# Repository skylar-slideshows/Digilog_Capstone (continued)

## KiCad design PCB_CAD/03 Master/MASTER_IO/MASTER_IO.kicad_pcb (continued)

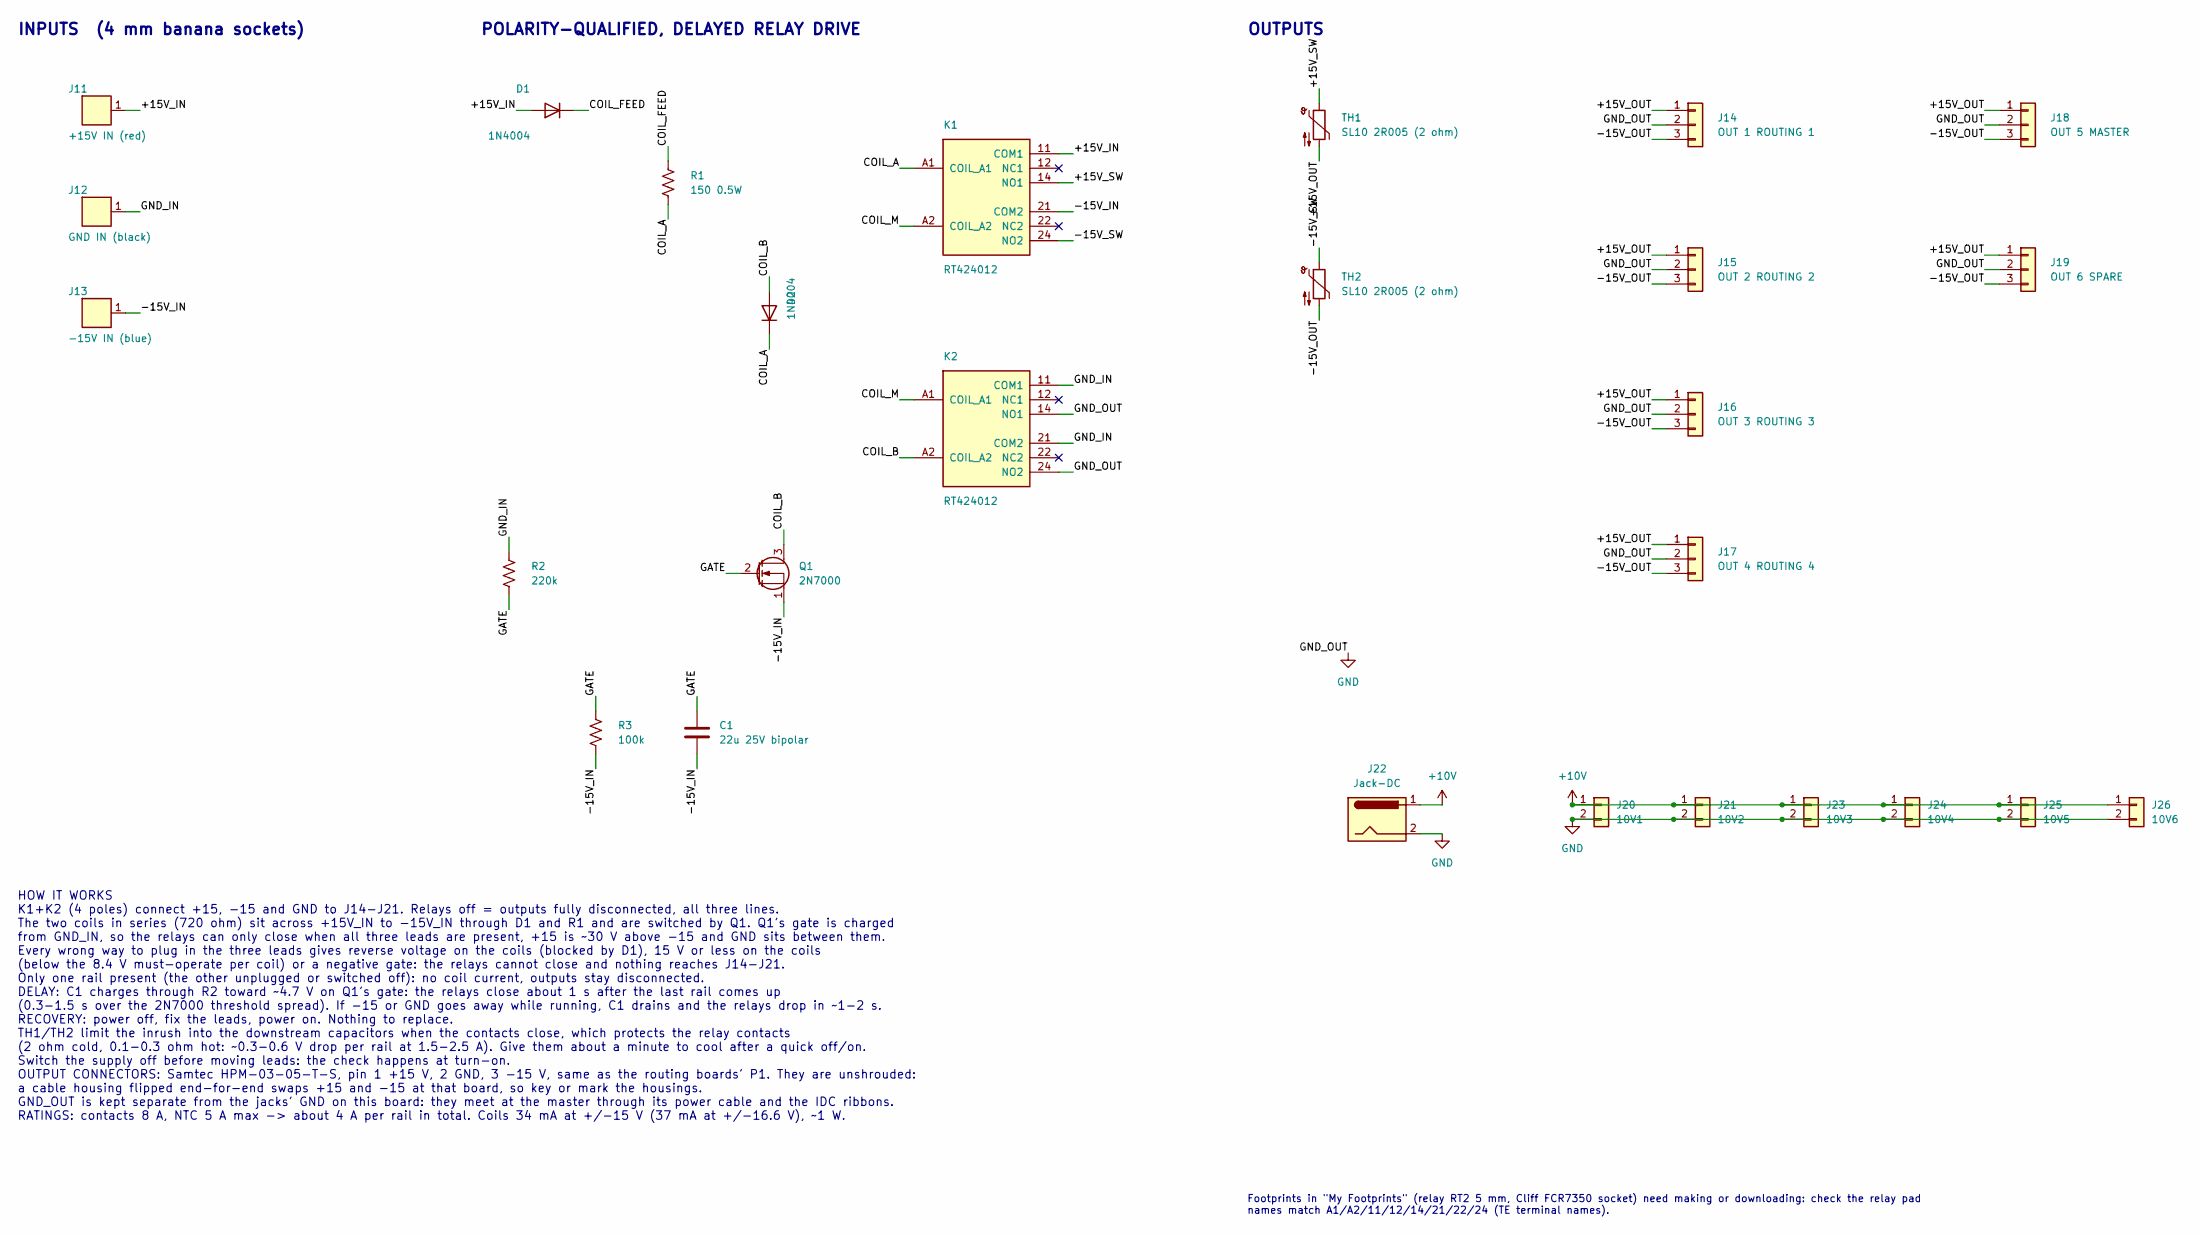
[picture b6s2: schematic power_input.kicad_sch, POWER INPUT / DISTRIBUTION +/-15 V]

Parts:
C1: 22u 25V bipolar; C_Radial_D6.3mm_H11.0mm_P2.50mm; MPN ECA-1EEN220
D1, D2: 1N4004; D_DO-41_SOD81_P10.16mm_Horizontal; MPN 1N4004G
J11: +15V IN (red); FCR7350; MPN FCR7350R
J12: GND IN (black); FCR7350; MPN FCR7350B
J13: -15V IN (blue); FCR7350; MPN FCR7350L
J14: OUT 1 ROUTING 1; Samtec_HPM-03-05-x-S_Straight_1x03_Pitch5.08mm; MPN HPM-03-05-T-S
J15: OUT 2 ROUTING 2; Samtec_HPM-03-05-x-S_Straight_1x03_Pitch5.08mm; MPN HPM-03-05-T-S
J16: OUT 3 ROUTING 3; Samtec_HPM-03-05-x-S_Straight_1x03_Pitch5.08mm; MPN HPM-03-05-T-S
J17: OUT 4 ROUTING 4; Samtec_HPM-03-05-x-S_Straight_1x03_Pitch5.08mm; MPN HPM-03-05-T-S
J18: OUT 5 MASTER; Samtec_HPM-03-05-x-S_Straight_1x03_Pitch5.08mm; MPN HPM-03-05-T-S
J19: OUT 6 SPARE; Samtec_HPM-03-05-x-S_Straight_1x03_Pitch5.08mm; MPN HPM-03-05-T-S
J20: 10V1; PinHeader_1x02_P2.54mm_Vertical
J21: 10V2; PinHeader_1x02_P2.54mm_Vertical
J22: Jack-DC; BarrelJack_Horizontal
J23: 10V3; PinHeader_1x02_P2.54mm_Vertical
J24: 10V4; PinHeader_1x02_P2.54mm_Vertical
J25: 10V5; PinHeader_1x02_P2.54mm_Vertical
J26: 10V6; PinHeader_1x02_P2.54mm_Vertical
K1, K2: RT424012; Relay_DPDT_Schrack-RT2-FormC_RM5mm; MPN RT424012
Q1: 2N7000; TO-92_Inline_Wide; MPN 2N7000
R1: 150 0.5W; R_Axial_DIN0309_L9.0mm_D3.2mm_P12.70mm_Horizontal; MPN MFR50SFTE52-150R
R2: 220k; R_Axial_DIN0207_L6.3mm_D2.5mm_P10.16mm_Horizontal; MPN MFR-25FBF52-220K
R3: 100k; R_Axial_DIN0207_L6.3mm_D2.5mm_P10.16mm_Horizontal; MPN MFR-25FBF52-100K
TH1, TH2: SL10 2R005 (2 ohm); C_Disc_D10.0mm_W2.5mm_P5.00mm; MPN SL10 2R005

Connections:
+10V: J20.1, J21.1, J22.1, J23.1, J24.1, J25.1, J26.1
/POWER INPUT +/-15V/+15V_IN: D1.2 (A), J11.1 (~_1), K1.11 (COM1)
/POWER INPUT +/-15V/+15V_OUT: J14.1, J15.1, J16.1, J17.1, J18.1, J19.1, TH1.2
/POWER INPUT +/-15V/+15V_SW: K1.14 (NO1), TH1.1
/POWER INPUT +/-15V/-15V_IN: C1.2, J13.1 (~_1), K1.21 (COM2), Q1.1 (S), R3.2
/POWER INPUT +/-15V/-15V_OUT: J14.3, J15.3, J16.3, J17.3, J18.3, J19.3, TH2.2
/POWER INPUT +/-15V/-15V_SW: K1.24 (NO2), TH2.1
/POWER INPUT +/-15V/COIL_A: D2.1 (K), K1.A1 (COIL_A1), R1.2
/POWER INPUT +/-15V/COIL_B: D2.2 (A), K2.A2 (COIL_A2), Q1.3 (D)
/POWER INPUT +/-15V/COIL_FEED: D1.1 (K), R1.1
/POWER INPUT +/-15V/COIL_M: K1.A2 (COIL_A2), K2.A1 (COIL_A1)
/POWER INPUT +/-15V/GATE: C1.1, Q1.2 (G), R2.2, R3.1
/POWER INPUT +/-15V/GND_IN: J12.1 (~_1), K2.11 (COM1), K2.21 (COM2), R2.1
GND: J14.2, J15.2, J16.2, J17.2, J18.2, J19.2, J20.2, J21.2, J22.2, J23.2, J24.2, J25.2, J26.2, K2.14 (NO1), K2.24 (NO2); also elsewhere on the board

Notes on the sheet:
INPUTS (4 mm banana sockets)
HOW IT WORKS K1+K2 (4 poles) connect +15, -15 and GND to J14-J21. Relays off = outputs fully disconnected, all three lines. The two coils in series (720 ohm) sit across +15V_IN to -15V_IN through D1 and R1 and are switched by Q1. Q1's gate is charged from GND_IN, so the relays can only close when a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
POLARITY-QUALIFIED, DELAYED RELAY DRIVE
OUTPUTS
Footprints in "My Footprints" (relay RT2 5 mm, Cliff FCR7350 socket) need making or downloading: check the relay pad names match A1/A2/11/12/14/21/22/24 (TE terminal names).

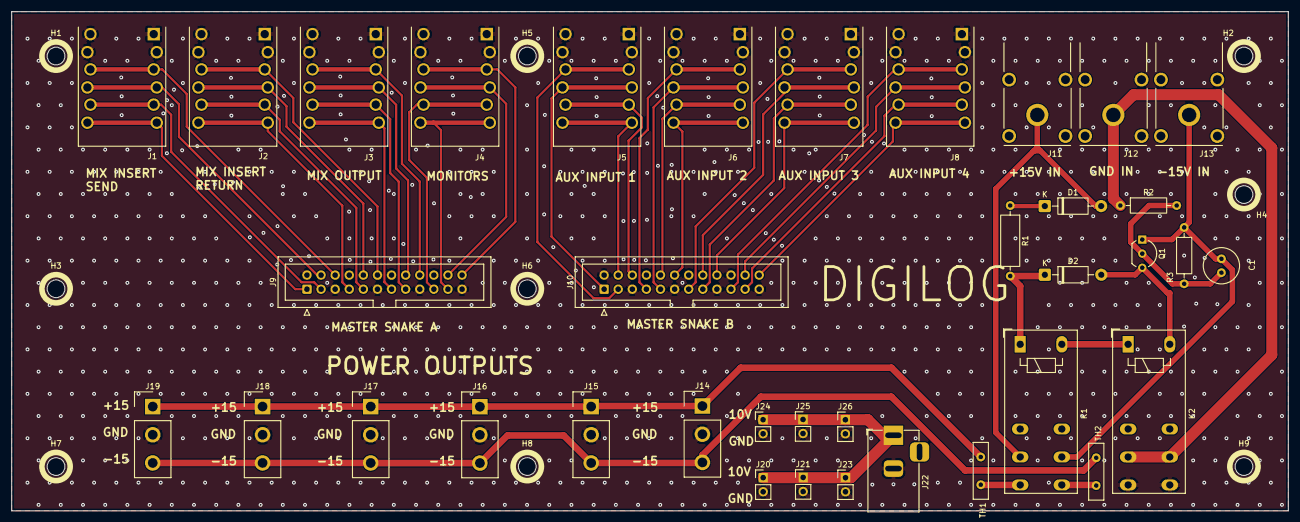
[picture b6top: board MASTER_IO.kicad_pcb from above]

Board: 2 copper layers, 230.0 x 89.9 mm, 46 parts (0 on the bottom side), 46 nets.

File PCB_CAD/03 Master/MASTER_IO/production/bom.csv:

Designator,Footprint,Quantity,Value,LCSC Part #
C1,C_Radial_D6.3mm_H11.0mm_P2.50mm,1,22u 25V bipolar,ECA-1EEN220
"D1, D2",D_DO-41_SOD81_P10.16mm_Horizontal,2,1N4004,1N4004G
J1,ACJS-MHDC,1,MIX_INSERT_SEND,ACJS-MHDC
J10,IDC-Header_2x12_P2.54mm_Vertical,1,AUX_IN,
J11,FCR7350,1,+15V IN (red),FCR7350R
J12,FCR7350,1,GND IN (black),FCR7350B
J13,FCR7350,1,-15V IN (blue),FCR7350L
J14,Samtec_HPM-03-05-x-S_Straight_1x03_Pitch5.08mm,1,OUT 1 ROUTING 1,HPM-03-05-T-S
J15,Samtec_HPM-03-05-x-S_Straight_1x03_Pitch5.08mm,1,OUT 2 ROUTING 2,HPM-03-05-T-S
J16,Samtec_HPM-03-05-x-S_Straight_1x03_Pitch5.08mm,1,OUT 3 ROUTING 3,HPM-03-05-T-S
J17,Samtec_HPM-03-05-x-S_Straight_1x03_Pitch5.08mm,1,OUT 4 ROUTING 4,HPM-03-05-T-S
J18,Samtec_HPM-03-05-x-S_Straight_1x03_Pitch5.08mm,1,OUT 5 MASTER,HPM-03-05-T-S
J19,Samtec_HPM-03-05-x-S_Straight_1x03_Pitch5.08mm,1,OUT 6 SPARE,HPM-03-05-T-S
J2,ACJS-MHDC,1,MIX_INSERT_RTN,ACJS-MHDC
J20,PinHeader_1x02_P2.54mm_Vertical,1,10V1,
J21,PinHeader_1x02_P2.54mm_Vertical,1,10V2,
J22,BarrelJack_Horizontal,1,Jack-DC,
J23,PinHeader_1x02_P2.54mm_Vertical,1,10V3,
J24,PinHeader_1x02_P2.54mm_Vertical,1,10V4,
J25,PinHeader_1x02_P2.54mm_Vertical,1,10V5,
J26,PinHeader_1x02_P2.54mm_Vertical,1,10V6,
J3,ACJS-MHDC,1,MIX_OUT,ACJS-MHDC
J4,ACJS-MHDC,1,MONITOR_OUT,ACJS-MHDC
J5,ACJS-MHDC,1,AUX1_IN,ACJS-MHDC
J6,ACJS-MHDC,1,AUX2_IN,ACJS-MHDC
J7,ACJS-MHDC,1,AUX3_IN,ACJS-MHDC
J8,ACJS-MHDC,1,AUX4_IN,ACJS-MHDC
J9,IDC-Header_2x12_P2.54mm_Vertical,1,MASTER_IO,
"K1, K2",Relay_DPDT_Schrack-RT2-FormC_RM5mm,2,RT424012,RT424012
Q1,TO-92_Inline_Wide,1,2N7000,2N7000
R1,R_Axial_DIN0309_L9.0mm_D3.2mm_P12.70mm_Horizontal,1,150 0.5W,MFR50SFTE52-150R
R2,R_Axial_DIN0207_L6.3mm_D2.5mm_P10.16mm_Horizontal,1,220k,MFR-25FBF52-220K
R3,R_Axial_DIN0207_L6.3mm_D2.5mm_P10.16mm_Horizontal,1,100k,MFR-25FBF52-100K
"TH1, TH2",C_Disc_D10.0mm_W2.5mm_P5.00mm,2,SL10 2R005 (2 ohm),SL10 2R005

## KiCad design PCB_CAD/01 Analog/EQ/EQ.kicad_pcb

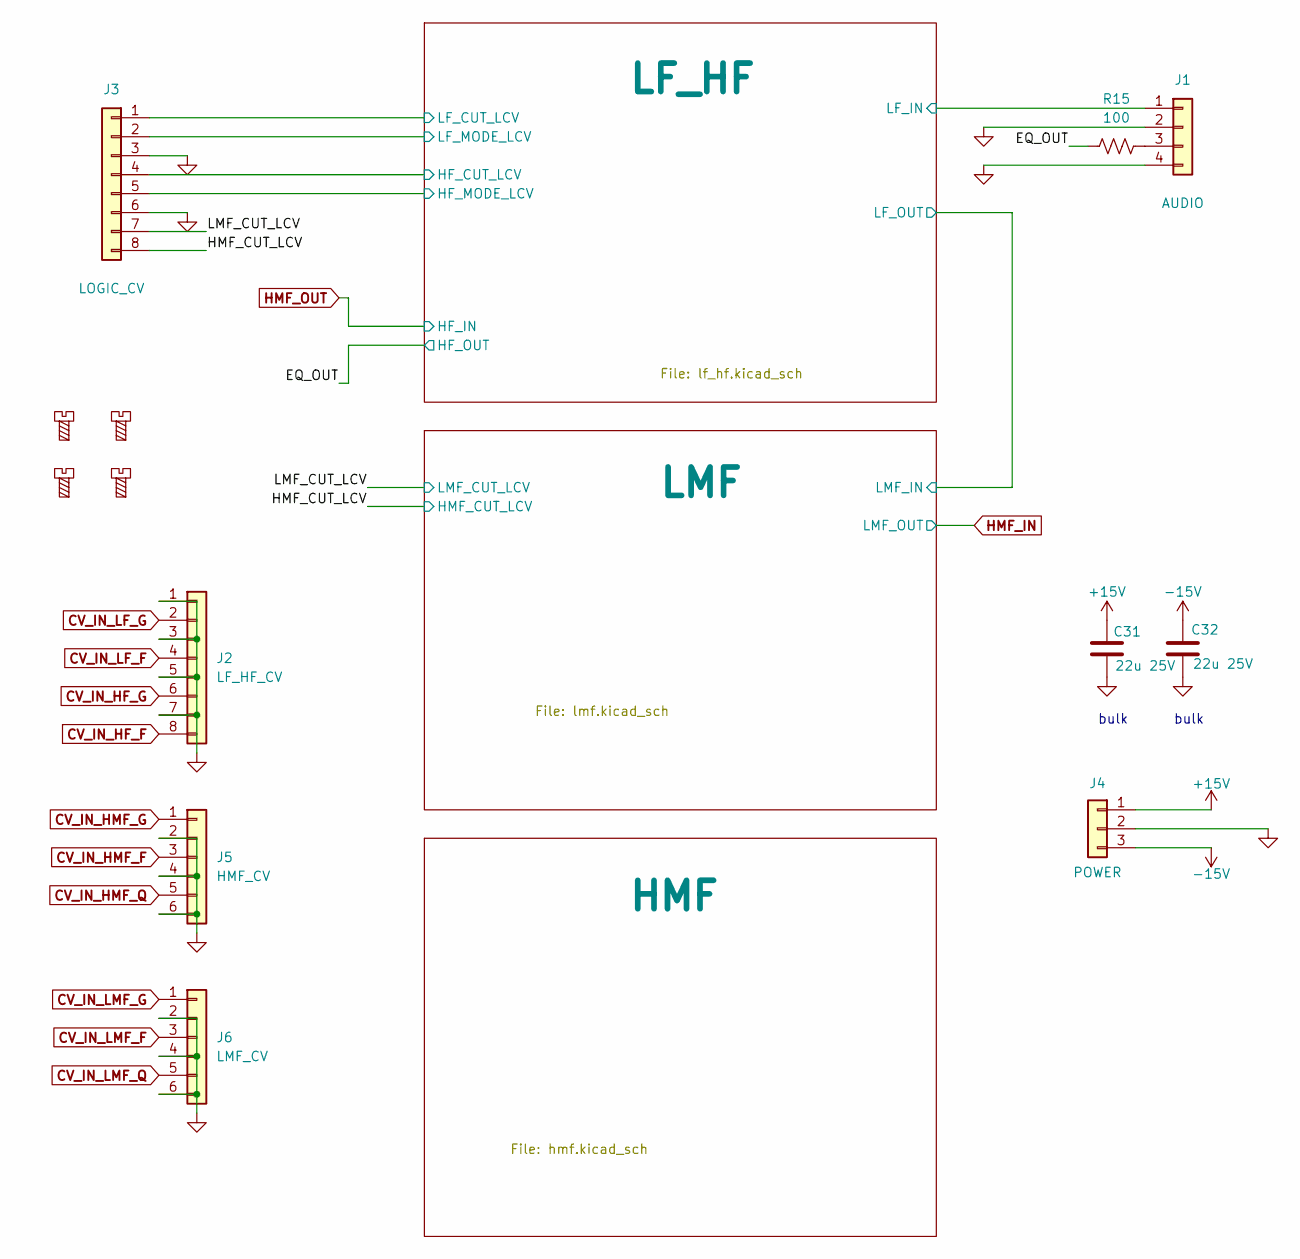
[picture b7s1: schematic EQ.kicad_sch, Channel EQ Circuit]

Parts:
C31, C32: 22u 25V; C_1210_3225Metric; LCSC C21397
H1, H2, H3, H4: MountingScrew; MountingHole_2.2mm_M2; LCSC dnp
J1: AUDIO; PinHeader_1x04_P2.54mm_Vertical; LCSC dnp
J2: LF_HF_CV; PinHeader_1x08_P2.54mm_Vertical; LCSC dnp
J3: LOGIC_CV; PinHeader_1x08_P2.54mm_Vertical; LCSC dnp
J4: POWER; PinHeader_1x03_P2.54mm_Vertical; LCSC dnp
J5: HMF_CV; PinHeader_1x06_P2.54mm_Vertical; LCSC dnp
J6: LMF_CV; PinHeader_1x06_P2.54mm_Vertical; LCSC dnp
R15: 100; R_0402_1005Metric; LCSC C317909

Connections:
+15V: C31.1, J4.1; also elsewhere on the board
-15V: C32.1, J4.3; also elsewhere on the board
/EQ_OUT: R15.1; also elsewhere on the board
/HMF_CUT_LCV: J3.8; also elsewhere on the board
/LF_HF/HF_CUT_LCV: J3.4; also elsewhere on the board
/LF_HF/HF_MODE_LCV: J3.5; also elsewhere on the board
/LF_HF/LF_CUT_LCV: J3.1; also elsewhere on the board
/LF_HF/LF_IN: J1.1; also elsewhere on the board
/LF_HF/LF_MODE_LCV: J3.2; also elsewhere on the board
/LMF_CUT_LCV: J3.7; also elsewhere on the board
CV_IN_HF_F: J2.8; also elsewhere on the board
CV_IN_HF_G: J2.6; also elsewhere on the board
CV_IN_HMF_F: J5.3; also elsewhere on the board
CV_IN_HMF_G: J5.1; also elsewhere on the board
CV_IN_HMF_Q: J5.5; also elsewhere on the board
CV_IN_LF_F: J2.4; also elsewhere on the board
CV_IN_LF_G: J2.2; also elsewhere on the board
CV_IN_LMF_F: J6.3; also elsewhere on the board
CV_IN_LMF_G: J6.1; also elsewhere on the board
CV_IN_LMF_Q: J6.5; also elsewhere on the board
GND: C31.2, C32.2, J1.2, J1.4, J2.1, J2.3, J2.5, J2.7, J3.3, J3.6, J4.2, J5.2, J5.4, J5.6, J6.2, J6.4, J6.6; also elsewhere on the board
unnamed: J1.3, R15.2

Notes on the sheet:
bulk

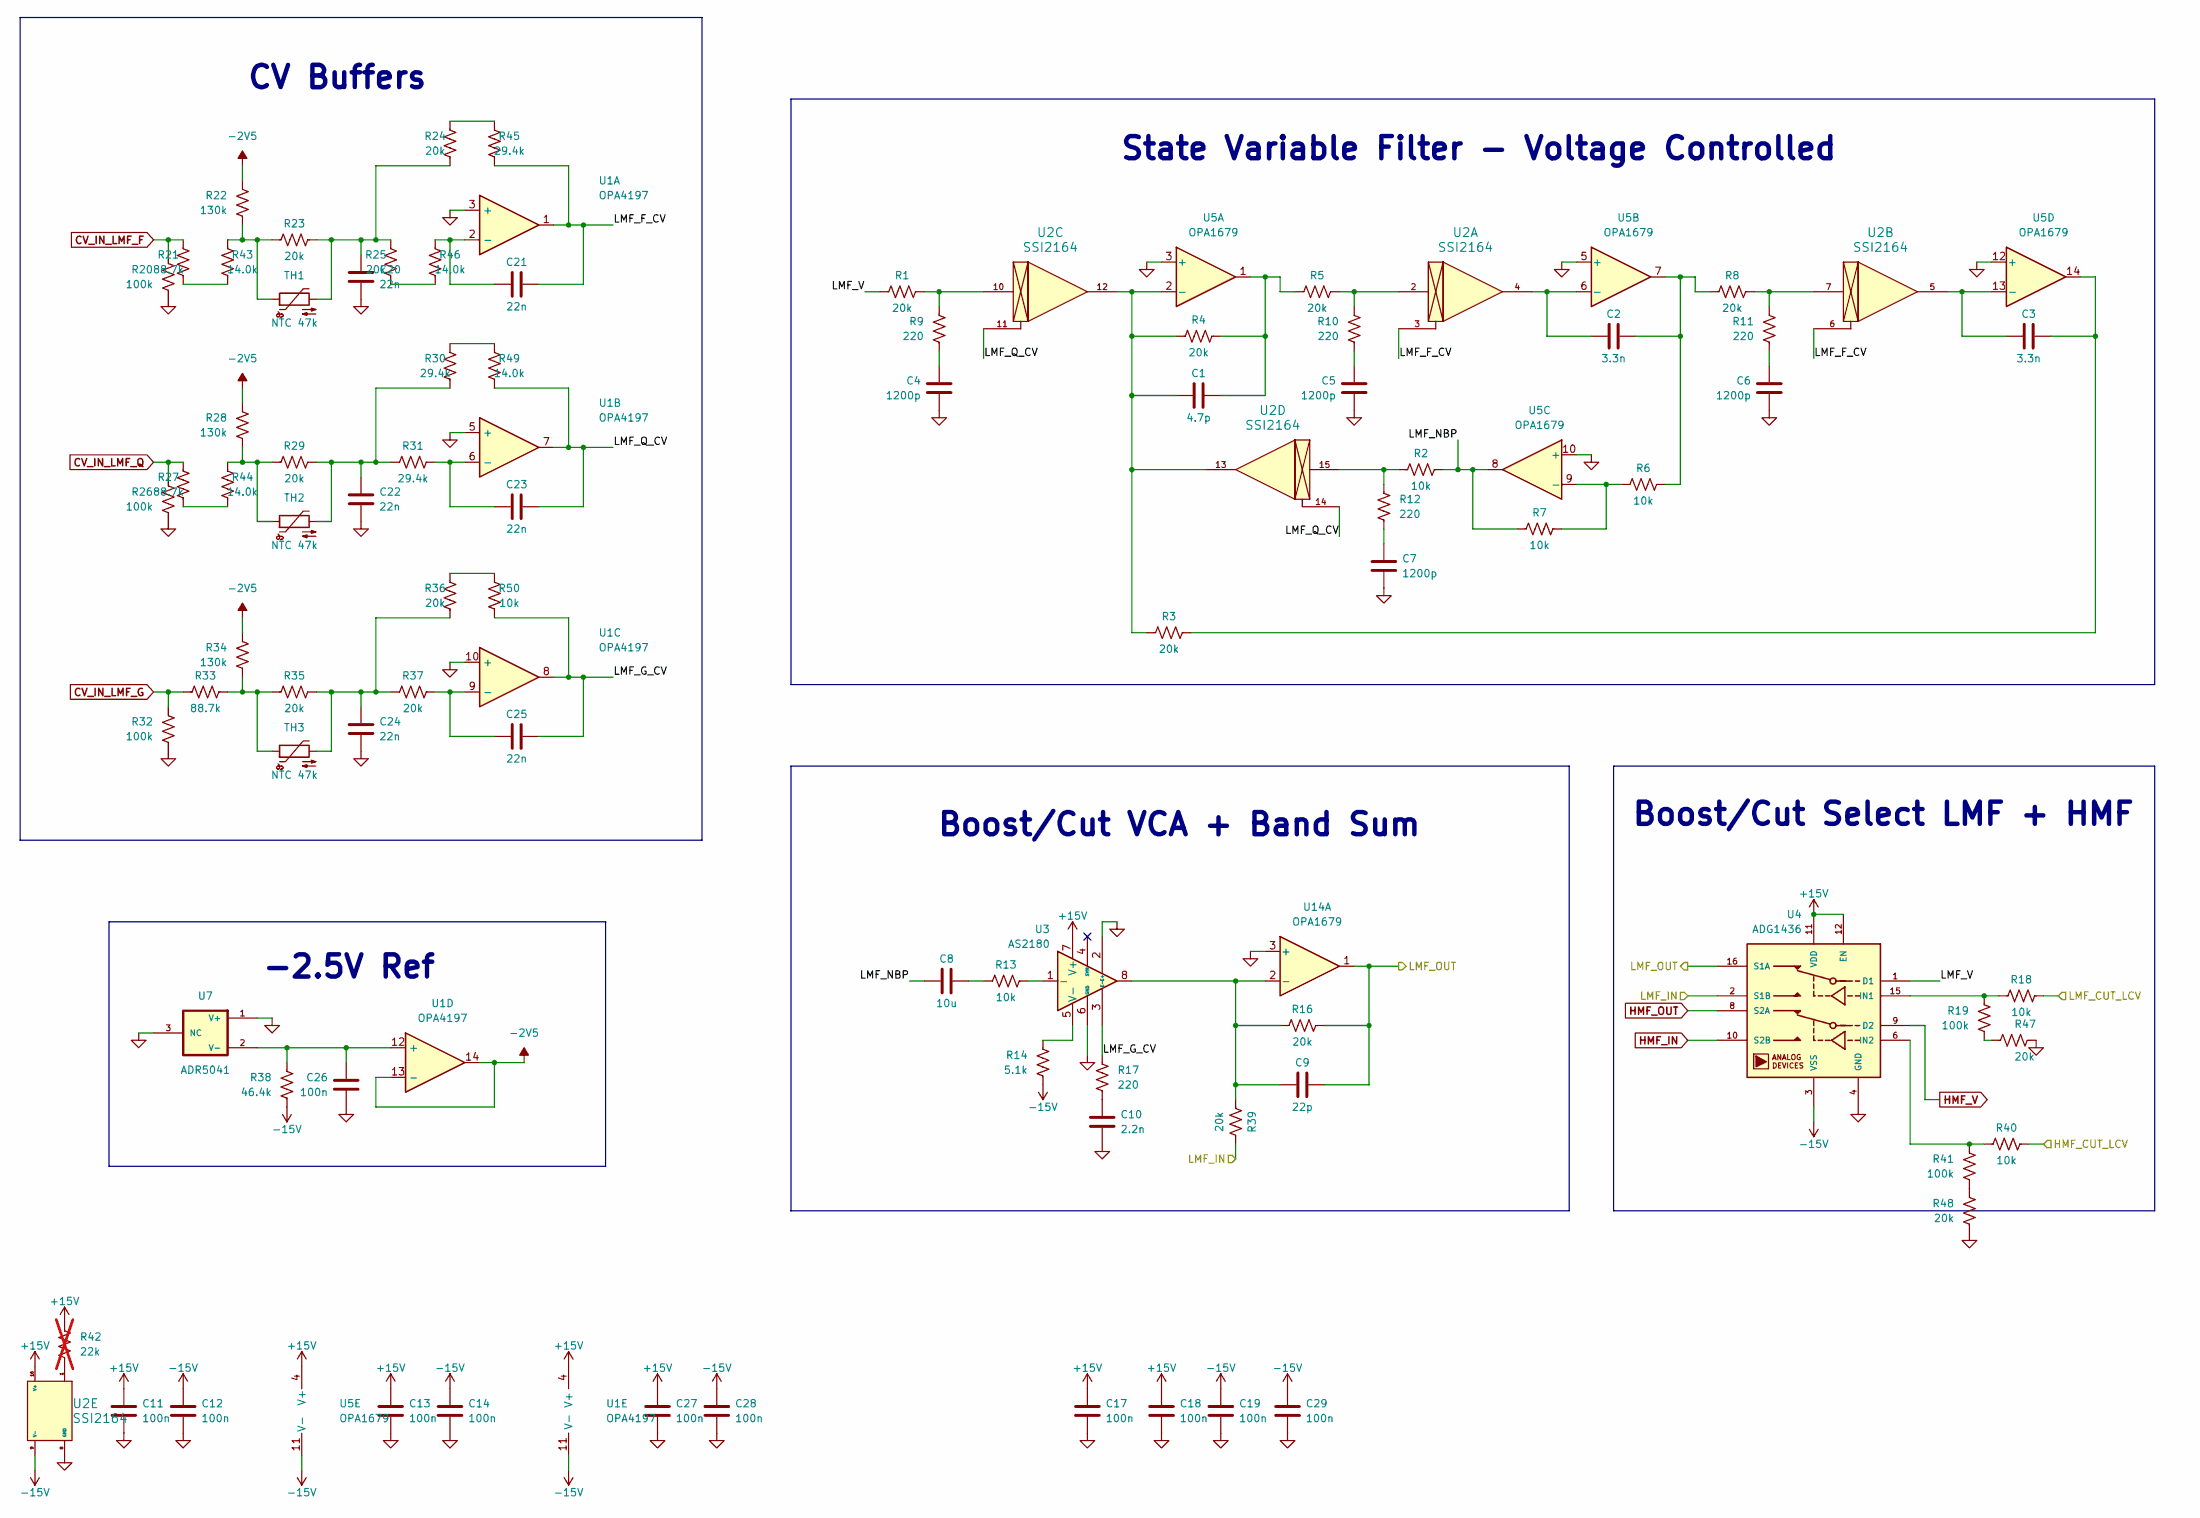
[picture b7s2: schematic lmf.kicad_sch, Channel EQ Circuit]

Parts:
C1: 4.7p; C_0603_1608Metric; LCSC C282071
C2, C3: 3.3n; C_0603_1608Metric; LCSC C107048
C4, C5, C6, C7: 1200p; C_1206_3216Metric; LCSC C527278
C8: 10u; CP_Elec_6.3x5.4_Nichicon; LCSC C340735
C9: 22p; C_0603_1608Metric; LCSC C105620
C10: 2.2n; C_0805_2012Metric; LCSC C107103
C11, C12, C13, C14, C17, C18, C19, C27, C28, C29: 100n; C_0603_1608Metric; LCSC C1591
C20, C21, C22, C23, C24, C25: 22n; C_1206_3216Metric; LCSC C7500389
C26: 100n; C_0603_1608Metric; LCSC C1590
R1, R3, R4, R5, R8, R16, R23, R24, R25, R29, R35, R36, R37, R39, R47, R48: 20k; R_0603_1608Metric; LCSC C311888
R2, R6, R7, R13, R18, R40, R50: 10k; R_0603_1608Metric; LCSC C95204
R9, R10, R11, R12, R17: 220; R_0603_1608Metric; LCSC C318124
R14: 5.1k; R_0603_1608Metric; LCSC C122969
R19, R20, R26, R32, R41: 100k; R_0603_1608Metric; LCSC C122538
R21, R27, R33: 88.7k; R_0603_1608Metric; LCSC C728599
R22, R28, R34: 130k; R_0603_1608Metric; LCSC C473257
R30, R31, R45: 29.4k; R_0603_1608Metric; LCSC C667085
R38: 46.4k; R_0603_1608Metric; LCSC C861420
R42: 22k; R_0603_1608Metric; LCSC C335085; not fitted
R43, R44, R46, R49: 14.0k; R_0603_1608Metric; LCSC C705941
TH1, TH2, TH3: NTC 47k; R_Axial_DIN0207_L6.3mm_D2.5mm_P2.54mm_Vertical; MPN NTCLE100E3473JB0; LCSC dnp
U1: OPA4197; SOIC-14_3.9x8.7mm_P1.27mm; LCSC C2058532
U2: SSI2164; SSI2164_breakout; LCSC dnp
U3: AS2180; PinHeader_1x08_P2.54mm_Vertical; LCSC dnp
U4: ADG1436; Analog_LFCSP-16-1EP_4x4mm_P0.65mm_EP2.1x2.1mm; LCSC C655227
U5, U14: OPA1679; SOIC-14_3.9x8.7mm_P1.27mm; LCSC C2878631
U7: ADR5041; SOT-23; MPN ADR5041ARTZ-R2; LCSC C659596

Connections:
+15V: C11.1, C13.1, C17.1, C18.1, C27.1, R42.1, U1.4 (V+), U2.16 (V+), U3.7 (V+), U4.11 (VDD), U4.12 (EN), U5.4 (V+); also elsewhere on the board
-2V5: R22.1, R28.1, R34.1, U1.13 (-), U1.14; also elsewhere on the board
-15V: C12.1, C14.1, C19.1, C28.1, C29.1, R14.2, R38.2, U1.11 (V-), U2.9 (V-), U4.3 (VSS), U5.11 (V-); also elsewhere on the board
/HMF_CUT_LCV: R40.2; also elsewhere on the board
/LF_HF/LF_OUT: R39.2, U4.2 (S1B); also elsewhere on the board
/LMF/LMF_F_CV: C21.2, R45.2, U1.1, U2.3, U2.6
/LMF/LMF_G_CV: C25.2, R17.1, R50.2, U1.8, U3.3 (E-)
/LMF/LMF_NBP: C8.1, R2.2, R7.1, U5.8
/LMF/LMF_Q_CV: C23.2, R49.2, U1.7, U2.11, U2.14
/LMF/LMF_V: R1.1, U4.1 (D1)
/LMF_CUT_LCV: R18.2; also elsewhere on the board
CV_IN_LMF_F: R20.1, R21.1; also elsewhere on the board
CV_IN_LMF_G: R32.1, R33.1; also elsewhere on the board
CV_IN_LMF_Q: R26.1, R27.1; also elsewhere on the board
GND: C4.2, C5.2, C6.2, C7.2, C10.2, C11.2, C12.2, C13.2, C14.2, C17.2, C18.2, C19.2, C20.2, C22.2, C24.2, C26.2, C27.2, C28.2, C29.2, R20.2, R26.2, R32.2, R47.2, R48.2, U1.3 (+), U1.5 (+), U1.10 (+), U2.8 (GND), U3.2 (E+), U3.6 (GND), U4.4 (GND), U5.3 (+), U5.5 (+), U5.10 (+), U5.12 (+), U7.1 (V+), U7.3 (NC), U14.3 (+); also elsewhere on the board
HMF_IN: C9.2, R16.2, U4.10 (S2B), U4.16 (S1A), U14.1; also elsewhere on the board
HMF_OUT: U4.8 (S2A); also elsewhere on the board
HMF_V: U4.9 (D2); also elsewhere on the board
unnamed: C1.2, R4.2, R5.1, U5.1
unnamed: C2.2, R6.2, R8.1, U5.7
unnamed: C3.2, R3.2, U5.14
unnamed: C4.1, R9.2
unnamed: C5.1, R10.2
unnamed: C6.1, R11.2
unnamed: C7.1, R12.2
unnamed: C8.2, R13.1
unnamed: C10.1, R17.2
unnamed: C20.1, R23.2, R24.1, R25.1, TH1.2
unnamed: C22.1, R29.2, R30.1, R31.1, TH2.2
unnamed: C24.1, R35.2, R36.1, R37.1, TH3.2
unnamed: R1.2, R9.1, U2.10
unnamed: R5.2, R10.1, U2.2
unnamed: R8.2, R11.1, U2.7
unnamed: R2.1, R12.1, U2.15
unnamed: R19.2, R47.1
unnamed: R21.2, R43.1
unnamed: R22.2, R23.1, R43.2, TH1.1
unnamed: R24.2, R45.1
unnamed: R25.2, R46.1
unnamed: R27.2, R44.1
unnamed: R28.2, R29.1, R44.2, TH2.1
unnamed: R30.2, R49.1
unnamed: R33.2, R34.2, R35.1, TH3.1
unnamed: R36.2, R50.1
unnamed: R41.2, R48.1
unnamed: R42.2, U2.1
unnamed: C21.1, R46.2, U1.2 (-)
unnamed: C23.1, R31.2, U1.6 (-)
unnamed: C25.1, R37.2, U1.9 (-)
unnamed: C26.1, R38.1, U1.12 (+), U7.2 (V-)
unnamed: R13.2, U3.1 (-)
unnamed: R14.1, U3.5 (V-)
unnamed: R18.1, R19.1, U4.15 (IN1)
unnamed: R40.1, R41.1, U4.6 (IN2)
unnamed: C1.1, R3.1, R4.1, U2.12, U2.13, U5.2 (-)
unnamed: C2.1, U2.4, U5.6 (-)
unnamed: R6.1, R7.2, U5.9 (-)
unnamed: C3.1, U2.5, U5.13 (-)
unnamed: C9.1, R16.1, R39.1, U3.8, U14.2 (-)

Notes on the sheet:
Boost/Cut Select LMF + HMF
Boost/Cut VCA + Band Sum
-2.5V Ref
State Variable Filter - Voltage Controlled
CV Buffers

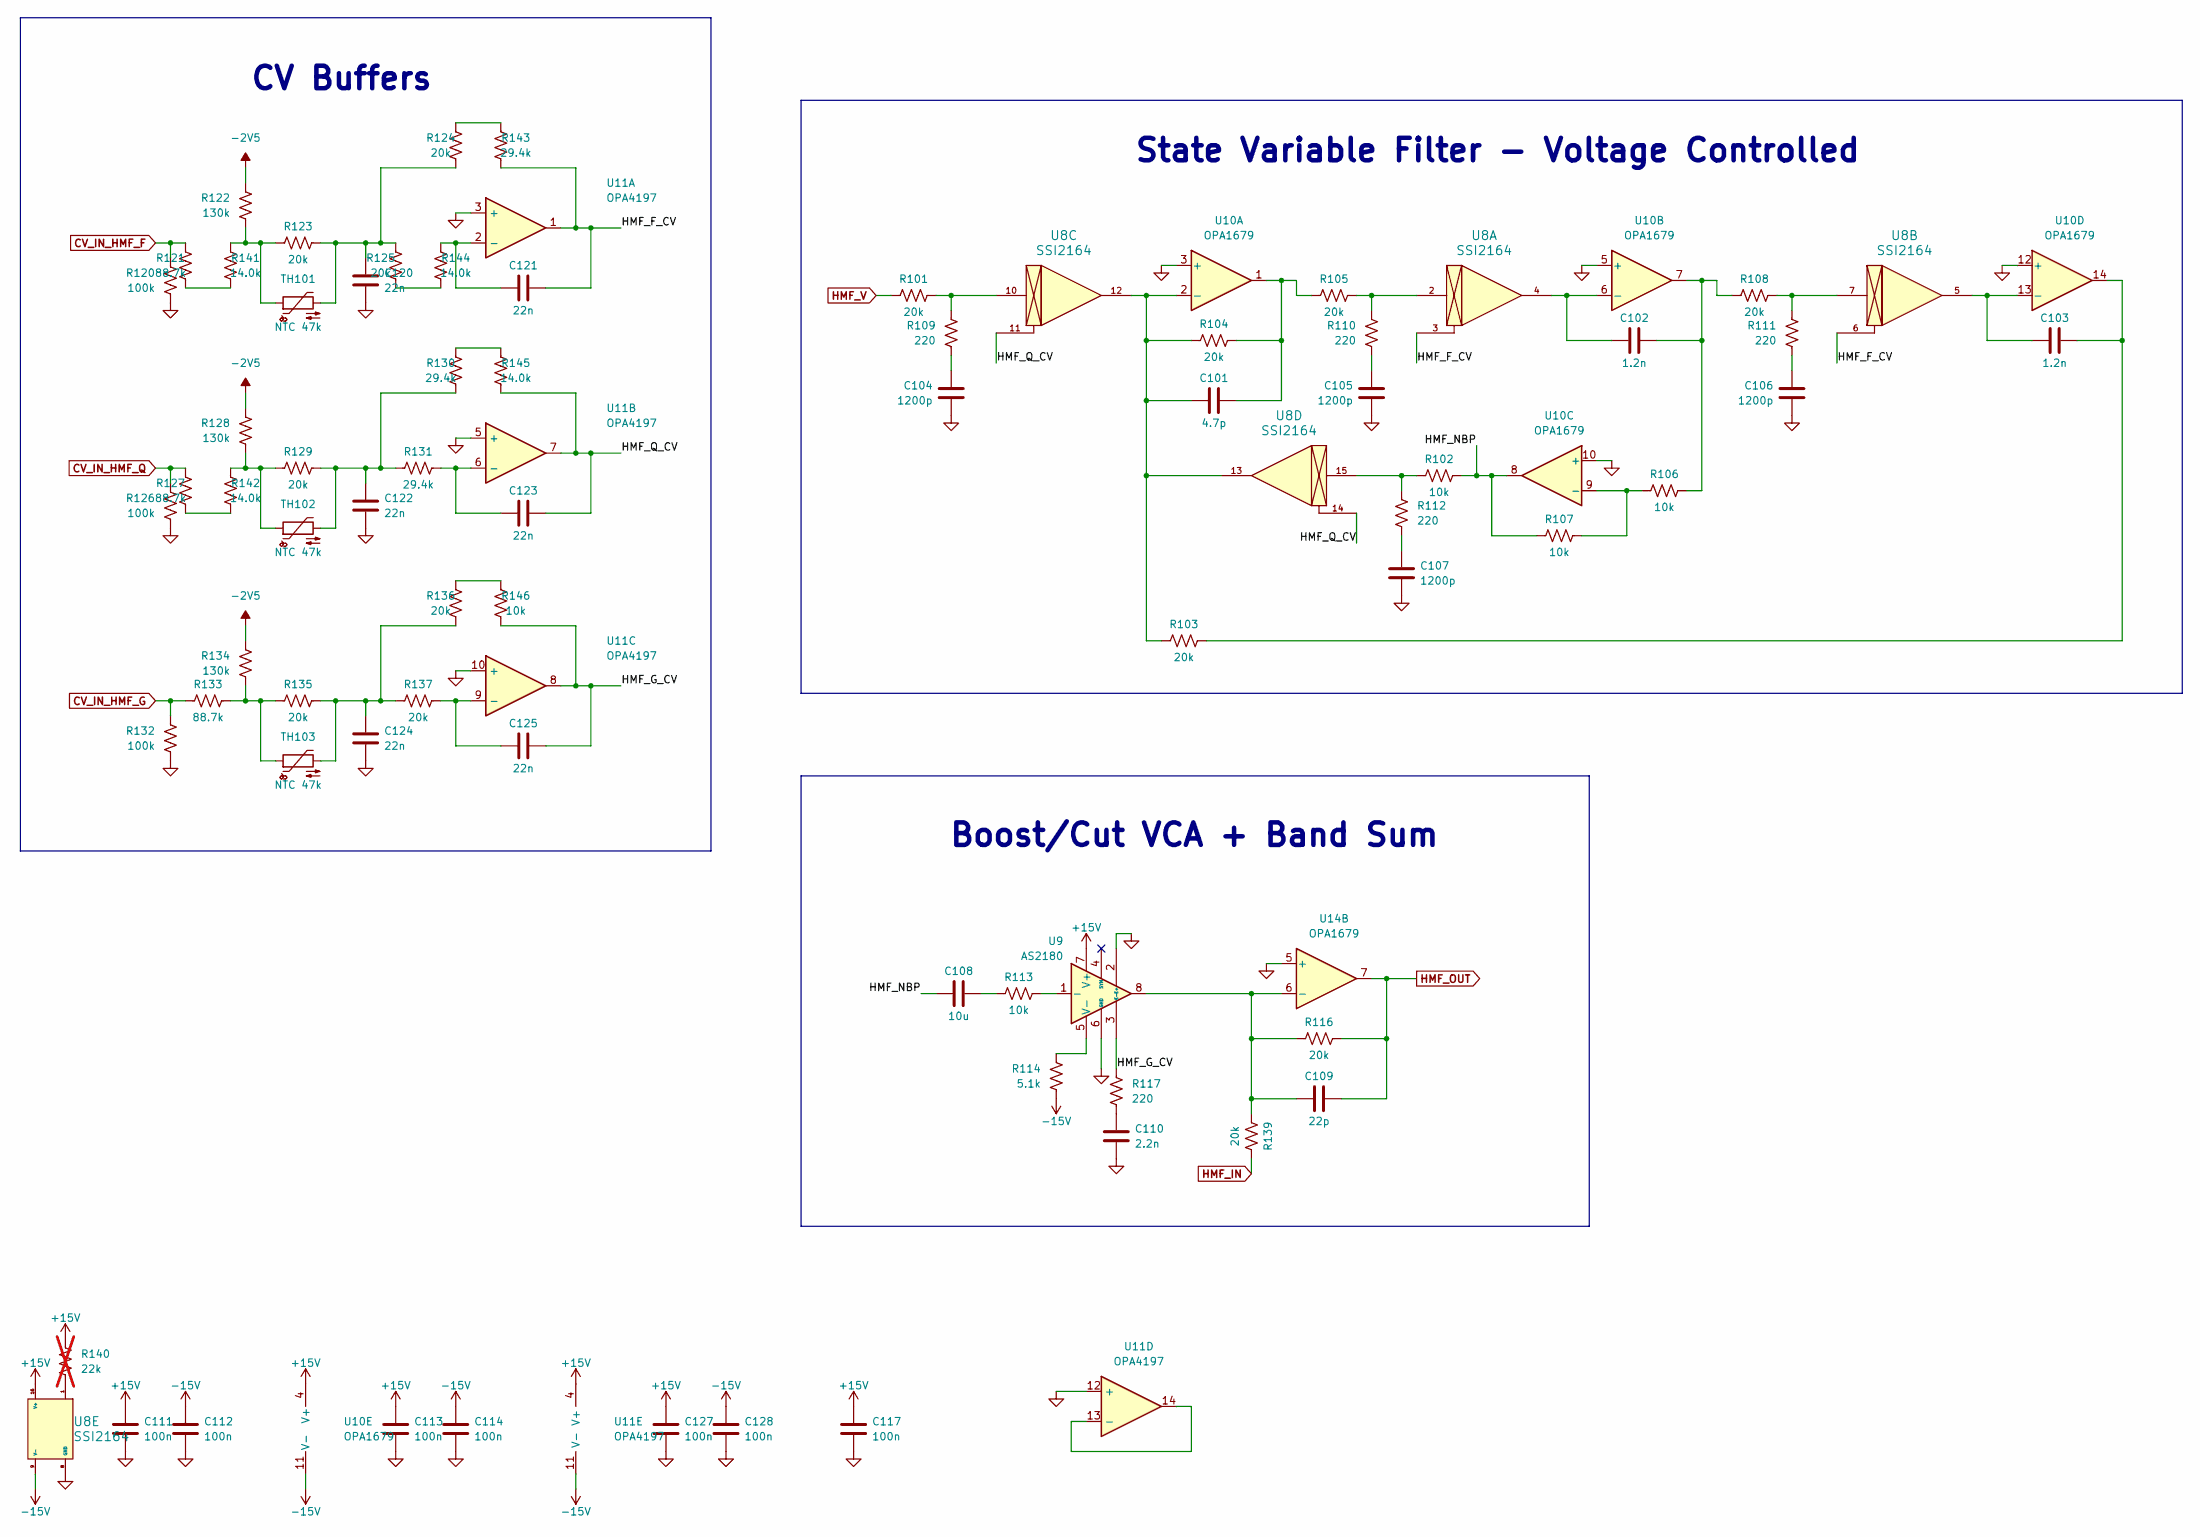
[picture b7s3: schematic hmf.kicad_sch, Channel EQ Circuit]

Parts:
C101: 4.7p; C_0603_1608Metric; LCSC C282071
C102, C103: 1.2n; C_1206_3216Metric; LCSC C527278
C104, C105, C106, C107: 1200p; C_1206_3216Metric; LCSC C527278
C108: 10u; CP_Elec_6.3x5.4_Nichicon; LCSC C340735
C109: 22p; C_0603_1608Metric; LCSC C105620
C110: 2.2n; C_0805_2012Metric; LCSC C107103
C111, C112, C113, C114, C117, C127, C128: 100n; C_0603_1608Metric; LCSC C1591
C120, C121, C122, C123, C124, C125: 22n; C_1206_3216Metric; LCSC C7500389
R101, R103, R104, R105, R108, R116, R123, R124, R125, R129, R135, R136, R137, R139: 20k; R_0603_1608Metric; LCSC C311888
R102, R106, R107, R113, R146: 10k; R_0603_1608Metric; LCSC C95204
R109, R110, R111, R112, R117: 220; R_0603_1608Metric; LCSC C318124
R114: 5.1k; R_0603_1608Metric; LCSC C122969
R120, R126, R132: 100k; R_0603_1608Metric; LCSC C122538
R121, R127, R133: 88.7k; R_0603_1608Metric; LCSC C728599
R122, R128, R134: 130k; R_0603_1608Metric; LCSC C473257
R130, R131, R143: 29.4k; R_0603_1608Metric; LCSC C667085
R140: 22k; R_0603_1608Metric; LCSC C335085; not fitted
R141, R142, R144, R145: 14.0k; R_0603_1608Metric; LCSC C705941
TH101, TH102, TH103: NTC 47k; R_Axial_DIN0207_L6.3mm_D2.5mm_P2.54mm_Vertical; MPN NTCLE100E3473JB0; LCSC dnp
U8: SSI2164; SSI2164_breakout; LCSC dnp
U9: AS2180; PinHeader_1x08_P2.54mm_Vertical; LCSC dnp
U10, U14: OPA1679; SOIC-14_3.9x8.7mm_P1.27mm; LCSC C2878631
U11: OPA4197; SOIC-14_3.9x8.7mm_P1.27mm; LCSC C2058532

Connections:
+15V: C111.1, C113.1, C117.1, C127.1, R140.1, U8.16 (V+), U9.7 (V+), U10.4 (V+), U11.4 (V+); also elsewhere on the board
-2V5: R122.1, R128.1, R134.1; also elsewhere on the board
-15V: C112.1, C114.1, C128.1, R114.2, U8.9 (V-), U10.11 (V-), U11.11 (V-); also elsewhere on the board
/HMF/HMF_F_CV: C121.2, R143.2, U8.3, U8.6, U11.1
/HMF/HMF_G_CV: C125.2, R117.1, R146.2, U9.3 (E-), U11.8
/HMF/HMF_NBP: C108.1, R102.2, R107.1, U10.8
/HMF/HMF_Q_CV: C123.2, R145.2, U8.11, U8.14, U11.7
CV_IN_HMF_F: R120.1, R121.1; also elsewhere on the board
CV_IN_HMF_G: R132.1, R133.1; also elsewhere on the board
CV_IN_HMF_Q: R126.1, R127.1; also elsewhere on the board
GND: C104.2, C105.2, C106.2, C107.2, C110.2, C111.2, C112.2, C113.2, C114.2, C117.2, C120.2, C122.2, C124.2, C127.2, C128.2, R120.2, R126.2, R132.2, U8.8 (GND), U9.2 (E+), U9.6 (GND), U10.3 (+), U10.5 (+), U10.10 (+), U10.12 (+), U11.3 (+), U11.5 (+), U11.10 (+), U11.12 (+), U14.5 (+); also elsewhere on the board
HMF_IN: R139.2; also elsewhere on the board
HMF_OUT: C109.2, R116.2, U14.7; also elsewhere on the board
HMF_V: R101.1; also elsewhere on the board
unnamed: C101.2, R104.2, R105.1, U10.1
unnamed: C102.2, R106.2, R108.1, U10.7
unnamed: C103.2, R103.2, U10.14
unnamed: C104.1, R109.2
unnamed: C105.1, R110.2
unnamed: C106.1, R111.2
unnamed: C107.1, R112.2
unnamed: C108.2, R113.1
unnamed: C110.1, R117.2
unnamed: C120.1, R123.2, R124.1, R125.1, TH101.2
unnamed: C122.1, R129.2, R130.1, R131.1, TH102.2
unnamed: C124.1, R135.2, R136.1, R137.1, TH103.2
unnamed: R101.2, R109.1, U8.10
unnamed: R102.1, R112.1, U8.15
unnamed: R105.2, R110.1, U8.2
unnamed: R108.2, R111.1, U8.7
unnamed: R121.2, R141.1
unnamed: R122.2, R123.1, R141.2, TH101.1
unnamed: R124.2, R143.1
unnamed: R125.2, R144.1
unnamed: R127.2, R142.1
unnamed: R128.2, R129.1, R142.2, TH102.1
unnamed: R130.2, R145.1
unnamed: R133.2, R134.2, R135.1, TH103.1
unnamed: R136.2, R146.1
unnamed: R140.2, U8.1
unnamed: R113.2, U9.1 (-)
unnamed: R114.1, U9.5 (V-)
unnamed: C101.1, R103.1, R104.1, U8.12, U8.13, U10.2 (-)
unnamed: C102.1, U8.4, U10.6 (-)
unnamed: R106.1, R107.2, U10.9 (-)
unnamed: C103.1, U8.5, U10.13 (-)
unnamed: C121.1, R144.2, U11.2 (-)
unnamed: C123.1, R131.2, U11.6 (-)
unnamed: C125.1, R137.2, U11.9 (-)
unnamed: U11.13 (-), U11.14
unnamed: C109.1, R116.1, R139.1, U9.8, U14.6 (-)

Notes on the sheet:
State Variable Filter - Voltage Controlled
CV Buffers
Boost/Cut VCA + Band Sum
